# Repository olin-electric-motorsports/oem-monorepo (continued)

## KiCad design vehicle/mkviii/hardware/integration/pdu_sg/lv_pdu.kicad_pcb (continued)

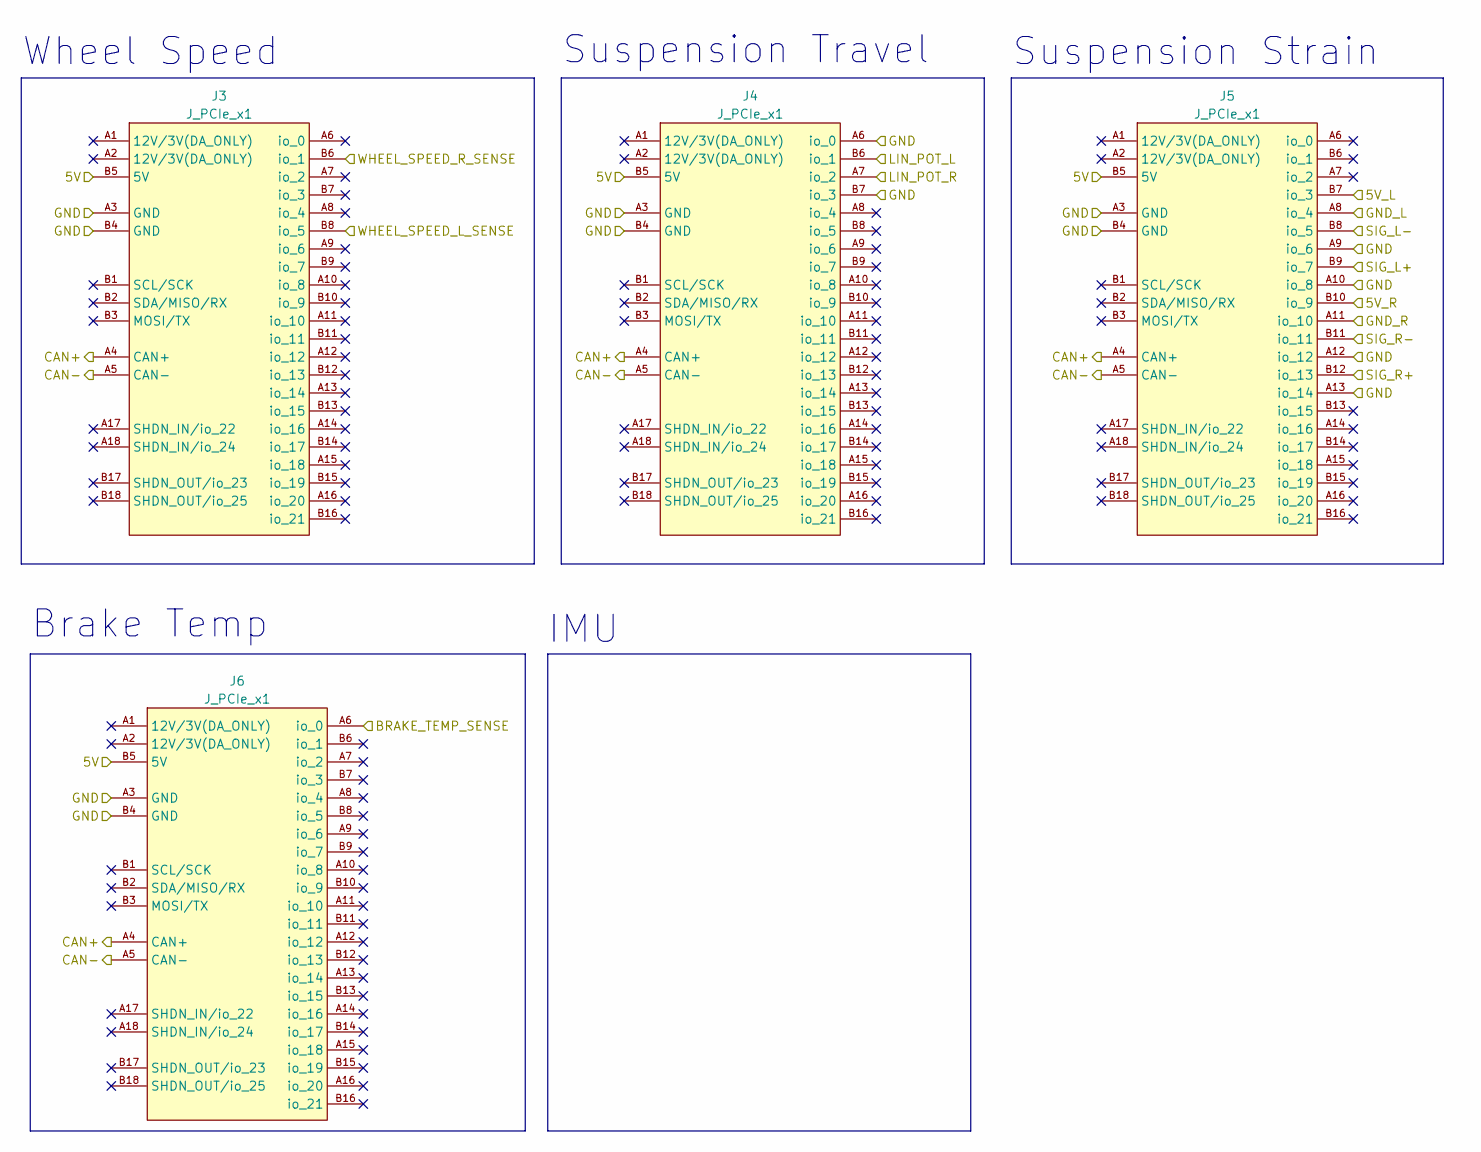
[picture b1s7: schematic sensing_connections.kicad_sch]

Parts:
J3, J4, J5, J6: J_PCIe_x1; MPN 2-1761465-1

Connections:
/BRAKE_TEMP_SIG: J6.A6 (io_0); also elsewhere on the board
/CAN_2+: J3.A4 (CAN+), J4.A4 (CAN+), J5.A4 (CAN+), J6.A4 (CAN+); also elsewhere on the board
/CAN_2-: J3.A5 (CAN-), J4.A5 (CAN-), J5.A5 (CAN-), J6.A5 (CAN-); also elsewhere on the board
/EXCITATION_L+: J5.B7 (io_3); also elsewhere on the board
/EXCITATION_L-: J5.A8 (io_4); also elsewhere on the board
/EXCITATION_R+: J5.B10 (io_9); also elsewhere on the board
/EXCITATION_R-: J5.A11 (io_10); also elsewhere on the board
/SIGNAL_L+: J5.B9 (io_7); also elsewhere on the board
/SIGNAL_L-: J5.B8 (io_5); also elsewhere on the board
/SIGNAL_R+: J5.B12 (io_13); also elsewhere on the board
/SIGNAL_R-: J5.B11 (io_11); also elsewhere on the board
/SUS_TRAVEL_L_SIG: J4.B6 (io_1); also elsewhere on the board
/SUS_TRAVEL_R_SIG: J4.A7 (io_2); also elsewhere on the board
/WHEEL_SPEED_L_SIG: J3.B8 (io_5); also elsewhere on the board
/WHEEL_SPEED_R_SIG: J3.B6 (io_1); also elsewhere on the board
GND: J3.A3 (GND), J3.B4 (GND), J4.A3 (GND), J4.A6 (io_0), J4.B4 (GND), J4.B7 (io_3), J5.A3 (GND), J5.A9 (io_6), J5.A10 (io_8), J5.A12 (io_12), J5.A13 (io_14), J5.B4 (GND), J6.A3 (GND), J6.B4 (GND); also elsewhere on the board

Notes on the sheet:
Brake Temp
Suspension Travel
IMU
Suspension Strain
Wheel Speed

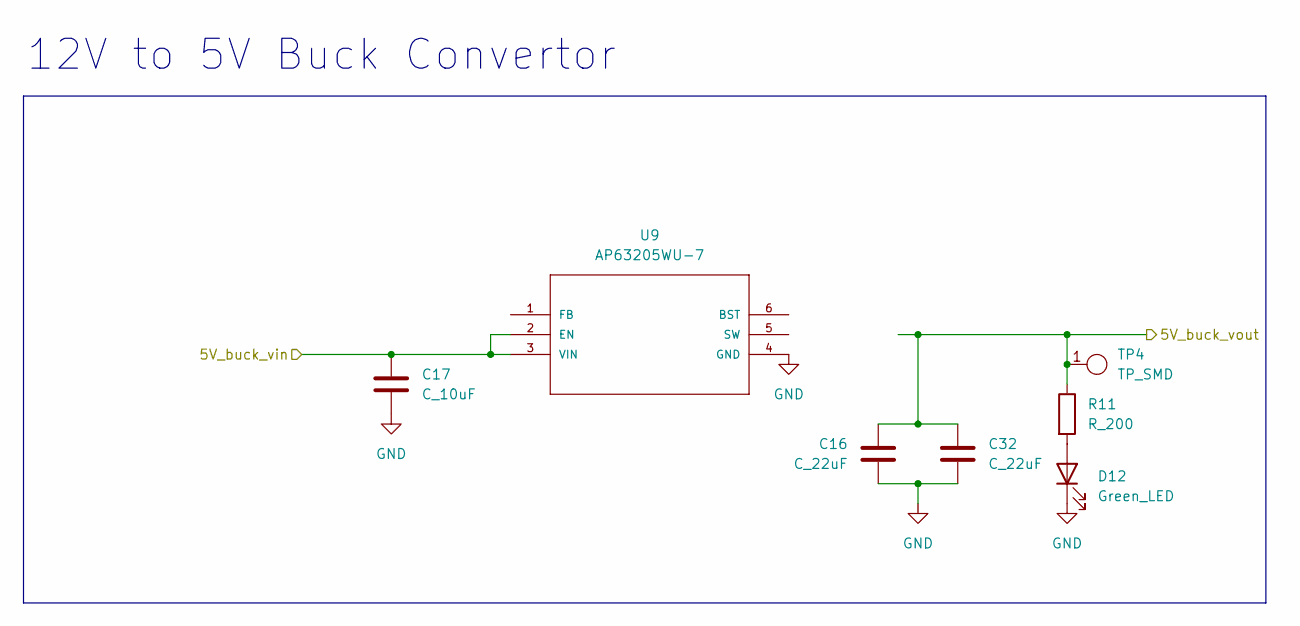
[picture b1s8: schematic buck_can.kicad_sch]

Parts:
C16, C32: C_22uF; C_1206_3216Metric; MPN CL31A226KAHNNNE
C17: C_10uF; C_0603_1608Metric; MPN GRM188D71A106KA73D
D12: Green_LED; D_0805_2012Metric; MPN LTST-C171KRKT
R11: R_200; R_0603_1608Metric; MPN WR06X2000FTL
TP4: TP_SMD; TP_Hook_SMD; MPN 5019
U9: AP63205WU-7; SOIC_05WU-7_DIO-M; MPN AP63205WU-7

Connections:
GND: C16.2, C17.2, C32.2, D12.1 (K), U9.1 (GND), U9.4 (GND); also elsewhere on the board
unnamed: D12.2 (A), R11.2

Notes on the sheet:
12V to 5V Buck Convertor

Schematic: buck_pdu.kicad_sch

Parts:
C18: C_10uF; C_0603_1608Metric; MPN GRM188D71A106KA73D
C19, C20: C_22uF; C_0603_1608Metric; MPN CL31A226KAHNNNE
C21: C_0.1uF; C_0603_1608Metric; MPN C0603C104Z4VACTU
D14: Green_LED; D_0805_2012Metric; MPN LTST-C170KGKT
L1: L_3.9uH; IND_BOURNS_SRR5018 (L_3.9uH_2A_55m_SMD); MPN SRR5018-3R9Y
R13: R_60.4; R_0603_1608Metric; MPN RMCF0603FT60R4
TP5: TP_SMD; TP_Hook_SMD; MPN 5019
U10: AP63203WU-7; SOT-23-6; MPN AP63203WU-7

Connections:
/low voltage distribution/3V3 buck/3V3_buck_vin: C18.1, U10.2 (EN), U10.3 (VIN)
/low voltage distribution/3V3 buck/3V3_buck_vout: C19.1, C20.1, L1.2, R13.1, TP5.1, U10.1 (FB)
GND: C18.2, C19.2, C20.2, D14.1 (K), U10.4 (GND); also elsewhere on the board
unnamed: D14.2 (A), R13.2
unnamed: C21.1, U10.6 (BST)
unnamed: C21.2, L1.1, U10.5 (SW)

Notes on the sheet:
12V to 3V3 Buck Converter

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
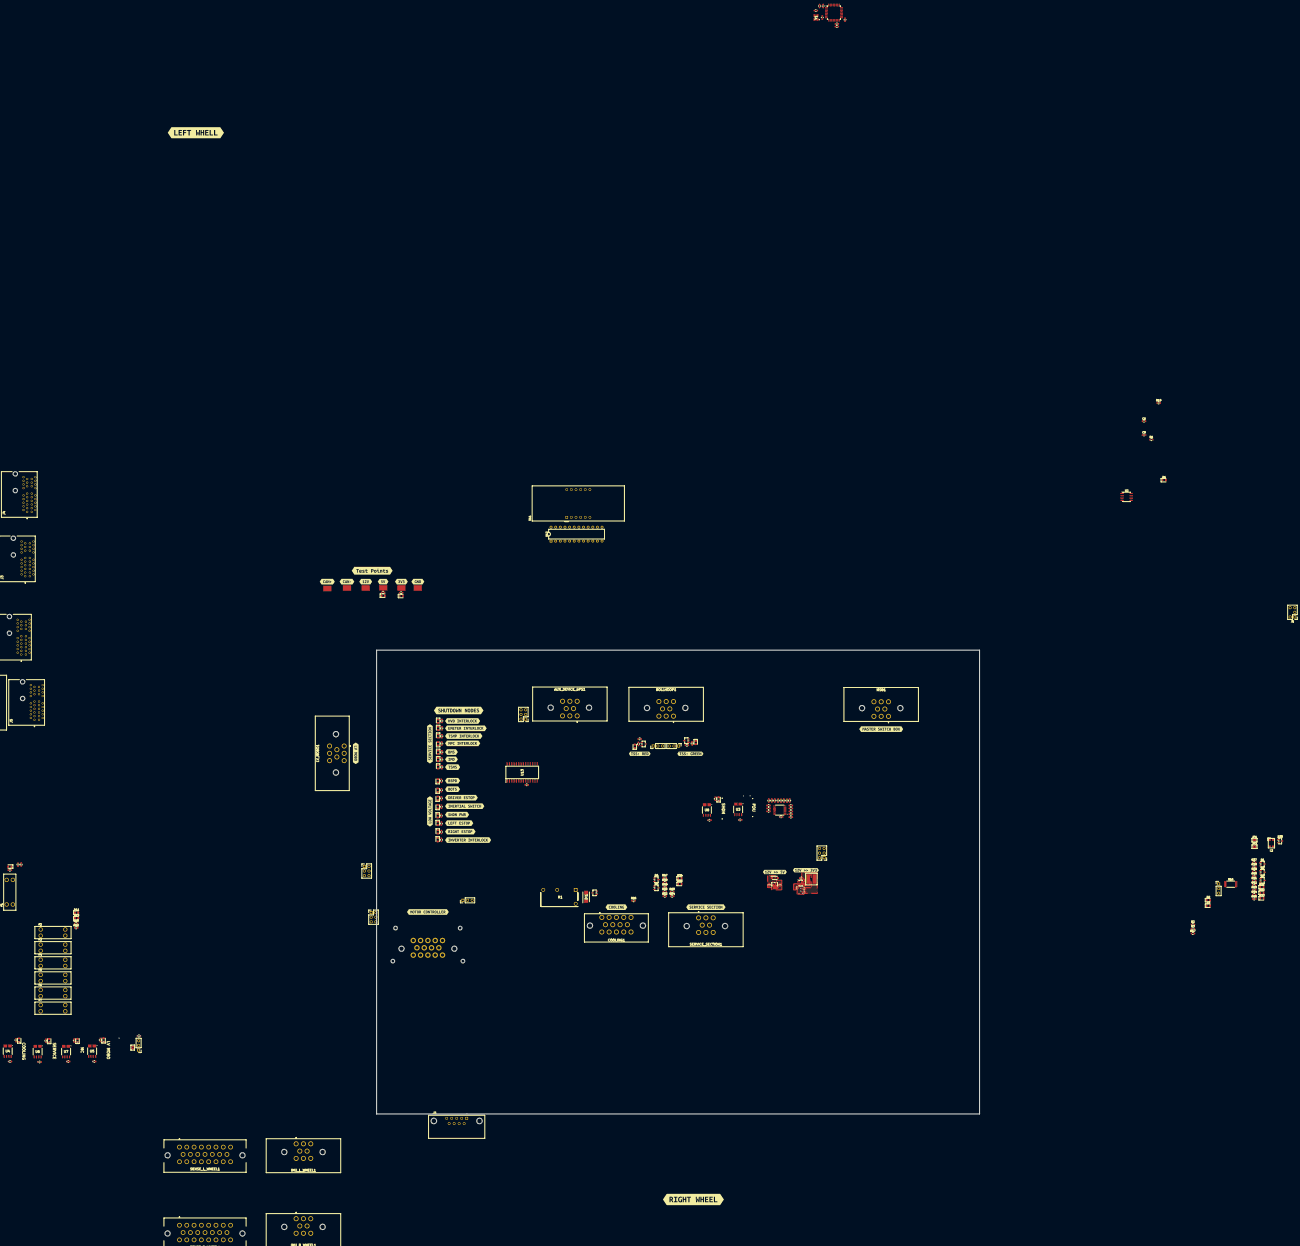
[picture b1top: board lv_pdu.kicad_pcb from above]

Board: 4 copper layers, 330.2 x 254.0 mm, 240 parts (1 on the bottom side), 169 nets.

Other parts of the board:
D10: D_100V_1A; SODFL3718X102N (D_Schottky_100V_1A_SMD - SS110LW)
kibuzzard-6AF3A9EF: G***; kibuzzard-6AF3A9EF
kibuzzard-6AF3AA3E: G***; kibuzzard-6AF3AA3E
kibuzzard-6AF3AA7C: G***; kibuzzard-6AF3AA7C
kibuzzard-6AF3AA54: G***; kibuzzard-6AF3AA54
kibuzzard-6AF3AA92: G***; kibuzzard-6AF3AA92
kibuzzard-6AF3AAA2: G***; kibuzzard-6AF3AAA2
kibuzzard-6AF3AB1F: G***; kibuzzard-6AF3AB1F
kibuzzard-6AF3AB02: G***; kibuzzard-6AF3AB02
kibuzzard-6AF3AB16: G***; kibuzzard-6AF3AB16
kibuzzard-6AF3AB30: G***; kibuzzard-6AF3AB30
kibuzzard-6AF3AC5A: G***; kibuzzard-6AF3AC5A
kibuzzard-6AF3AC21: G***; kibuzzard-6AF3AC21
kibuzzard-6AF3AC46: G***; kibuzzard-6AF3AC46
kibuzzard-6AF3AC51: G***; kibuzzard-6AF3AC51
kibuzzard-6AF3AC73: G***; kibuzzard-6AF3AC73
kibuzzard-6AF3AC82: G***; kibuzzard-6AF3AC82
kibuzzard-6AF3ACA7: G***; kibuzzard-6AF3ACA7
kibuzzard-6AF3ACE3: G***; kibuzzard-6AF3ACE3
kibuzzard-6AF3AD90: G***; kibuzzard-6AF3AD90
kibuzzard-6AF3ADBE: G***; kibuzzard-6AF3ADBE
kibuzzard-6AF3ADF4: G***; kibuzzard-6AF3ADF4
kibuzzard-6AF3AE7A: G***; kibuzzard-6AF3AE7A
kibuzzard-6AF3AEED: G***; kibuzzard-6AF3AEED
kibuzzard-6AF3AF2F: G***; kibuzzard-6AF3AF2F
kibuzzard-6AF3BEE3: G***; kibuzzard-6AF3BEE3
kibuzzard-6AF3BF1E: G***; kibuzzard-6AF3BF1E
kibuzzard-6AF3BF40: G***; kibuzzard-6AF3BF40
kibuzzard-6AF66EEA: G***; kibuzzard-6AF66EEA
kibuzzard-6AF66EF9: G***; kibuzzard-6AF66EF9
kibuzzard-6AF392A3: G***; kibuzzard-6AF392A3
kibuzzard-6AF392F1: G***; kibuzzard-6AF392F1
kibuzzard-6AF3934F: G***; kibuzzard-6AF3934F
kibuzzard-6AF3939E: G***; kibuzzard-6AF3939E
kibuzzard-6AF6706F: G***; kibuzzard-6AF6706F
kibuzzard-6AF6707D: G***; kibuzzard-6AF6707D
kibuzzard-6AF39264: G***; kibuzzard-6AF39264
kibuzzard-6AF39337: G***; kibuzzard-6AF39337
kibuzzard-6AF39365: G***; kibuzzard-6AF39365
kibuzzard-6AF67121: G***; kibuzzard-6AF67121
kibuzzard-6AFCE8DF: G***; kibuzzard-6AFCE8DF

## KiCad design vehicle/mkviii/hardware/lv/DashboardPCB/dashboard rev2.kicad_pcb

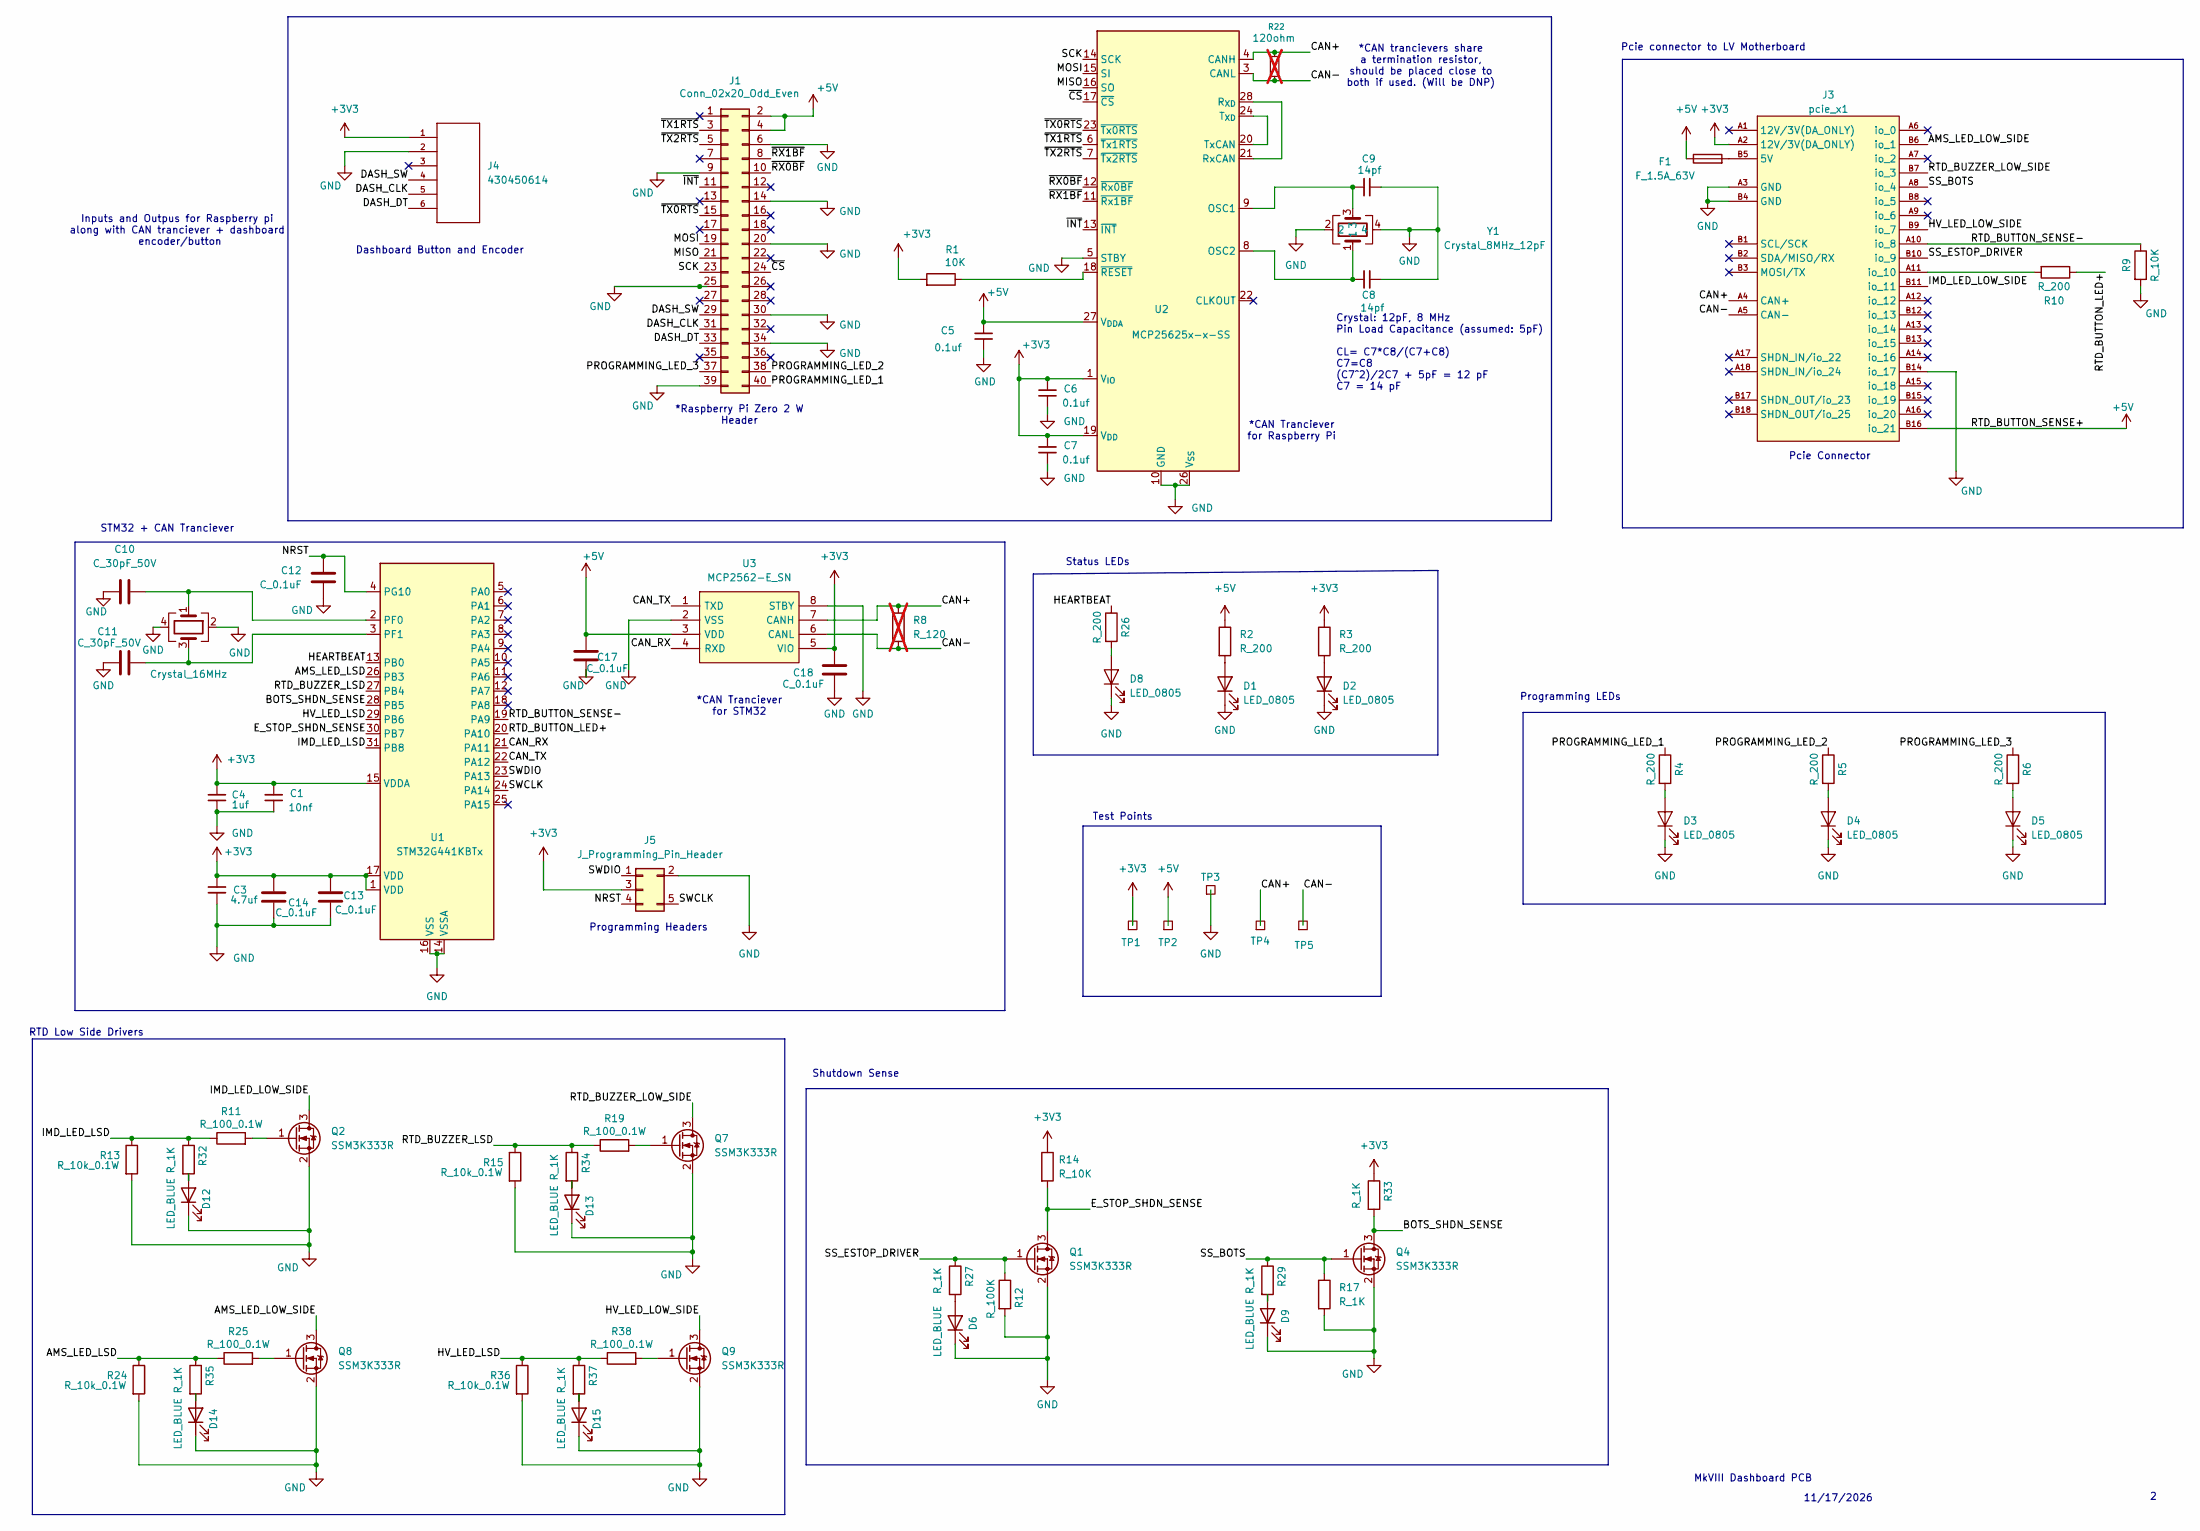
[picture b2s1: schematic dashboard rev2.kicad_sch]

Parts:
C1: 10nf; C_0603_1608Metric
C3: 4.7uf; C_0603_1608Metric
C4: 1uf; C_0603_1608Metric
C5, C6, C7: 0.1uf; C_0603_1608Metric
C8, C9: 14pf; C_0603_1608Metric
C10, C11: C_30pF_50V; C_0603_1608Metric; MPN CML0603C0G300JT50V
C12, C13, C14: C_0.1uF; C_0603_1608Metric; MPN CL10B104KB8NNWC
C17, C18: C_0.1uF; C_0603_1608Metric; MPN C0603C104Z4VACTU
D1, D2, D3, D4, D5, D8: LED_0805; D_0805_2012Metric; MPN 475-1410-1-ND
D6, D9, D12, D13, D14, D15: LED_BLUE; D_0805_2012Metric
F1: F_1.5A_63V; Fuse_1206_3216Metric; MPN 046601.5NR
J1: Conn_02x20_Odd_Even; PinHeader_2x20_P2.54mm_Vertical; MPN SFH11-PBPC-D20-ST-BK
J3: pcie_x1; BUS_PCIexpress_x1
J4: 430450614; MOLEX_0430450600; MANUFACTURER_PART_NUMBER 430450614
J5: J_Programming_Pin_Header; J_Programming_Pin_Header_Keyed
Q1, Q2, Q4, Q7, Q8, Q9: SSM3K333R; SOT-23; MPN SSM3K333RLFCT-ND
R1: 10K; R_0603_1608Metric_Pad0.98x0.95mm_HandSolder; MPN CRS0805-FX-1002ELFCT-ND
R2, R3, R4, R5, R6, R10, R26: R_200; R_0603_1608Metric_Pad0.98x0.95mm_HandSolder; MPN RMCF0805JT200RCT-ND
R8: R_120; R_0603_1608Metric; MPN RC0603FR-13120RL; not fitted
R9, R14: R_10K; R_0603_1608Metric_Pad0.98x0.95mm_HandSolder; MPN CRS0805-FX-1002ELFCT-ND
R11, R19, R25, R38: R_100_0.1W; R_0603_1608Metric; MPN RMCF0603FT100R
R12: R_100K; R_0603_1608Metric_Pad0.98x0.95mm_HandSolder; MPN P100KCCT-ND
R13, R15, R24, R36: R_10k_0.1W; R_0603_1608Metric; MPN RMCF0603FT10K0
R17, R27, R29, R32, R33, R34, R35, R37: R_1K; R_0603_1608Metric_Pad0.98x0.95mm_HandSolder; MPN RNCP0805FTD1K00CT-ND
R22: 120ohm; R_0402_1005Metric_Pad0.72x0.64mm_HandSolder; not fitted
TP1, TP2, TP3, TP4, TP5: TestPoint_Square; Test_Point_SMD
U1: STM32G441KBTx; LQFP-32_7x7mm_P0.8mm
U2: MCP25625x-x-SS; SSOP-28_5.3x10.2mm_P0.65mm
U3: MCP2562-E_SN; SOIC127P600X175-8N; Manufacturer_Part_Number MCP2562-E/SN; Mouser Part Number 579-MCP2562-E/SN
Y1: Crystal_8MHz_12pF; Crystal_TXC7M
Y2: Crystal_16MHz; Crystal_TXC7M; MPN 7M-16.000MAAJ-T

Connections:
+3V3: C1.1, C3.1, C4.1, C6.1, C7.1, C13.1, C14.1, C18.2, J3.A2 (12V/3V(DA_ONLY)), J4.1, J5.3, R1.2, R3.1, R14.1, R33.1, TP1.1 (1_1), U1.1 (VDD), U1.15 (VDDA), U1.17 (VDD), U2.1 (V_{IO}), U2.19 (V_{DD}), U3.5 (VIO)
+5V: C5.2, C17.2, F1.1, J1.2, J1.4, J3.B16 (io_21), R2.1, TP2.1 (1_1), U2.27 (V_{DDA}), U3.3 (VDD)
/AMS_LED_LOW_SIDE: J3.B6 (io_1), Q8.3 (D)
/AMS_LED_LSD: R24.1, R25.1, R35.1, U1.26 (PB3)
/BOTS_SHDN_SENSE: Q4.3 (D), R33.2, U1.28 (PB5)
/CAN+: J3.A4 (CAN+), R8.1, R22.1, TP4.1 (1_1), U2.4 (CANH), U3.7 (CANH)
/CAN-: J3.A5 (CAN-), R8.2, R22.2, TP5.1 (1_1), U2.3 (CANL), U3.6 (CANL)
/CAN_RX: U1.21 (PA11), U3.4 (RXD)
/CAN_TX: U1.22 (PA12), U3.1 (TXD)
/DASH_CLK: J1.31, J4.5
/DASH_DT: J1.33, J4.6
/DASH_SW: J1.29, J4.4
/E_STOP_SHDN_SENSE: Q1.3 (D), R14.2, U1.30 (PB7)
/HEARTBEAT: R26.1, U1.13 (PB0)
/HV_LED_LOW_SIDE: J3.B9 (io_7), Q9.3 (D)
/HV_LED_LSD: R36.1, R37.1, R38.1, U1.29 (PB6)
/IMD_LED_LOW_SIDE: J3.B11 (io_11), Q2.3 (D)
/IMD_LED_LSD: R11.1, R13.1, R32.1, U1.31 (PB8)
/MISO: J1.21, U2.16 (SO)
/MOSI: J1.19, U2.15 (SI)
/NRST: C12.1, J5.4, U1.4 (PG10)
/PROGRAMMING_LED_1: J1.40, R4.1
/PROGRAMMING_LED_2: J1.38, R5.1
/PROGRAMMING_LED_3: J1.37, R6.1
/RTD_BUTTON_LED+: R10.1, U1.20 (PA10)
/RTD_BUTTON_SENSE-: J3.A10 (io_8), R9.1, U1.19 (PA9)
/RTD_BUZZER_LOW_SIDE: J3.B7 (io_3), Q7.3 (D)
/RTD_BUZZER_LSD: R15.1, R19.1, R34.1, U1.27 (PB4)
/SCK: J1.23, U2.14 (SCK)
/SS_BOTS: J3.A8 (io_4), Q4.1 (G), R17.1, R29.1
/SS_ESTOP_DRIVER: J3.B10 (io_9), Q1.1 (G), R12.1, R27.1
/SWCLK: J5.5, U1.24 (PA14)
/SWDIO: J5.1, U1.23 (PA13)
/~CS: J1.24, U2.17 (~CS)
/~INT: J1.11, U2.13 (~INT)
/~RX0BF: J1.10, U2.12 (~Rx0BF)
/~RX1BF: J1.8, U2.11 (~Rx1BF)
/~TX0RTS: J1.15, U2.23 (~Tx0RTS)
/~TX1RTS: J1.3, U2.6 (~Tx1RTS)
/~TX2RTS: J1.5, U2.7 (~Tx2RTS)
GND: C1.2, C3.2, C4.2, C5.1, C6.2, C7.2, C8.1, C9.1, C10.1, C11.1, C12.2, C13.2, C14.2, C17.1, C18.1, D1.1 (K), D2.1 (K), D3.1 (K), D4.1 (K), D5.1 (K), D6.1 (K), D8.1 (K), D9.1 (K), D12.1 (K), D13.1 (K), D14.1 (K), D15.1 (K), J1.6, J1.9, J1.14, J1.20, J1.25, J1.30, J1.34, J1.39, J3.A3 (GND), J3.B4 (GND), J3.B14 (io_17), J4.2, J5.2, Q1.2 (S), Q2.2 (S), Q4.2 (S), Q7.2 (S), Q8.2 (S), Q9.2 (S), R9.2, R12.2, R13.2, R15.2, R17.2, R24.2, R36.2, TP3.1 (1_1), U1.14 (VSSA), U1.16 (VSS), U1.32 (VSS), U2.5 (STBY), U2.10 (GND), U2.26 (V_{SS}), U3.2 (VSS), U3.8 (STBY), Y1.2, Y1.4, Y2.2, Y2.4
unnamed: D1.2 (A), R2.2
unnamed: D2.2 (A), R3.2
unnamed: D3.2 (A), R4.2
unnamed: D4.2 (A), R5.2
unnamed: D5.2 (A), R6.2
unnamed: D6.2 (A), R27.2
unnamed: D8.2 (A), R26.2
unnamed: D9.2 (A), R29.2
unnamed: D12.2 (A), R32.2
unnamed: D13.2 (A), R34.2
unnamed: D14.2 (A), R35.2
unnamed: D15.2 (A), R37.2
unnamed: F1.2, J3.B5 (5V)
unnamed: J3.A11 (io_10), R10.2
unnamed: Q2.1 (G), R11.2
unnamed: Q7.1 (G), R19.2
unnamed: Q8.1 (G), R25.2
unnamed: Q9.1 (G), R38.2
unnamed: C10.2, U1.2 (PF0), Y2.1
unnamed: C11.2, U1.3 (PF1), Y2.3
unnamed: C9.2, U2.9 (OSC1), Y1.3
unnamed: C8.2, U2.8 (OSC2), Y1.1
unnamed: U2.21 (RxCAN), U2.28 (R_{XD})
unnamed: U2.20 (TxCAN), U2.24 (T_{XD})
unnamed: R1.1, U2.18 (~RESET)

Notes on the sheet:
MkVIII Dashboard PCB
*CAN Tranciever for STM32
*Raspberry Pi Zero 2 W Header
Shutdown Sense
Dashboard Button and Encoder
*CAN Tranciever for Raspberry Pi
Pcie connector to LV Motherboard
*CAN trancievers share a termination resistor, should be placed close to both if used. (Will be DNP)
Programming LEDs
RTD Low Side Drivers
Pcie Connector
Inputs and Outpus for Raspberry pi along with CAN tranciever + dashboard encoder/button
11/17/2026
Test Points
Status LEDs
Crystal: 12pF, 8 MHz Pin Load Capacitance (assumed: 5pF) CL= C7*C8/(C7+C8) C7=C8 (C7^2)/2C7 + 5pF = 12 pF C7 = 14 pF
Programming Headers
STM32 + CAN Tranciever

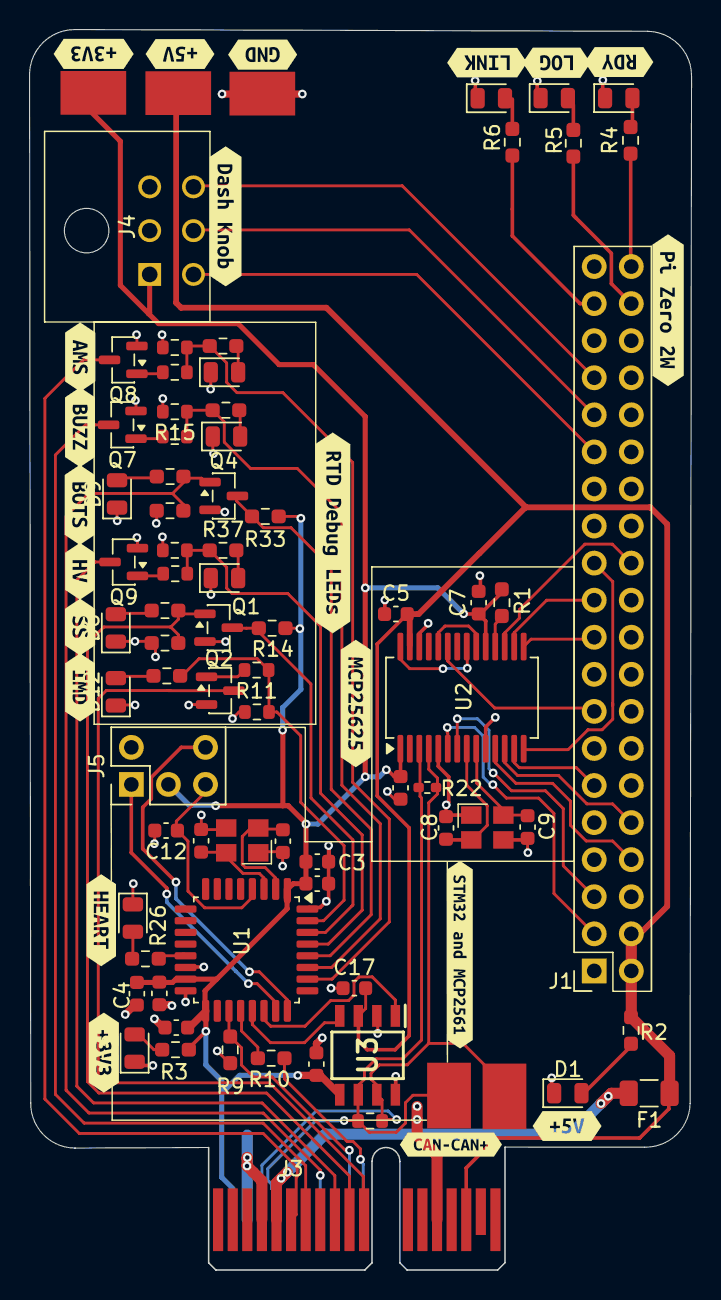
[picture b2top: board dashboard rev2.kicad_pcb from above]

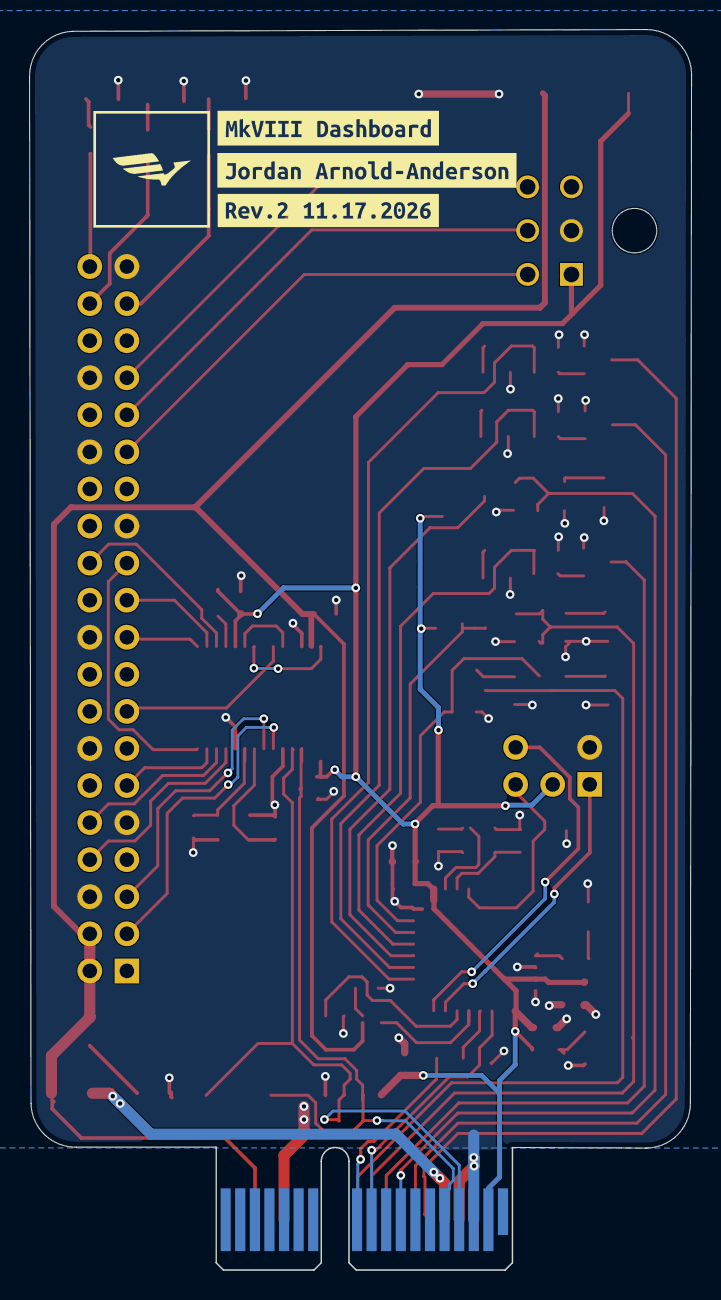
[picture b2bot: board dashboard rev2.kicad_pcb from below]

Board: 2 copper layers, 45.4 x 85.0 mm, 101 parts (4 on the bottom side), 66 nets.

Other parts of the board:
kibuzzard-6AF36B19: G***; kibuzzard-6AF36B19
kibuzzard-6AF76DEC: G***; kibuzzard-6AF76DEC
kibuzzard-6AF76E90: G***; kibuzzard-6AF76E90
kibuzzard-6AF76EA2: G***; kibuzzard-6AF76EA2
kibuzzard-6AF76EB9: G***; kibuzzard-6AF76EB9
kibuzzard-6AF76ED1: G***; kibuzzard-6AF76ED1
kibuzzard-6AF76EDC: G***; kibuzzard-6AF76EDC
kibuzzard-6AF76F0D: G***; kibuzzard-6AF76F0D
kibuzzard-6AF76F2E: G***; kibuzzard-6AF76F2E
kibuzzard-6AF76F8E: G***; kibuzzard-6AF76F8E
kibuzzard-6AF76F23: G***; kibuzzard-6AF76F23
kibuzzard-6AF76F53: G***; kibuzzard-6AF76F53
kibuzzard-6AF76F70: G***; kibuzzard-6AF76F70
kibuzzard-6AF76FEB: G***; kibuzzard-6AF76FEB
kibuzzard-6AF759B2: G***; kibuzzard-6AF759B2
kibuzzard-6AF771E8: G***; kibuzzard-6AF771E8
kibuzzard-6AF771FB: G***; kibuzzard-6AF771FB
kibuzzard-6AF7599B: G***; kibuzzard-6AF7599B
kibuzzard-6AF75395: G***; kibuzzard-6AF75395
kibuzzard-6AF75990: G***; kibuzzard-6AF75990
kibuzzard-6AF77199: G***; kibuzzard-6AF77199
kibuzzard-6AF77208: G***; kibuzzard-6AF77208
kibuzzard-6AFB7252: G***; kibuzzard-6AFB7252
kibuzzard-6AFF5868: G***; kibuzzard-6AFF5868

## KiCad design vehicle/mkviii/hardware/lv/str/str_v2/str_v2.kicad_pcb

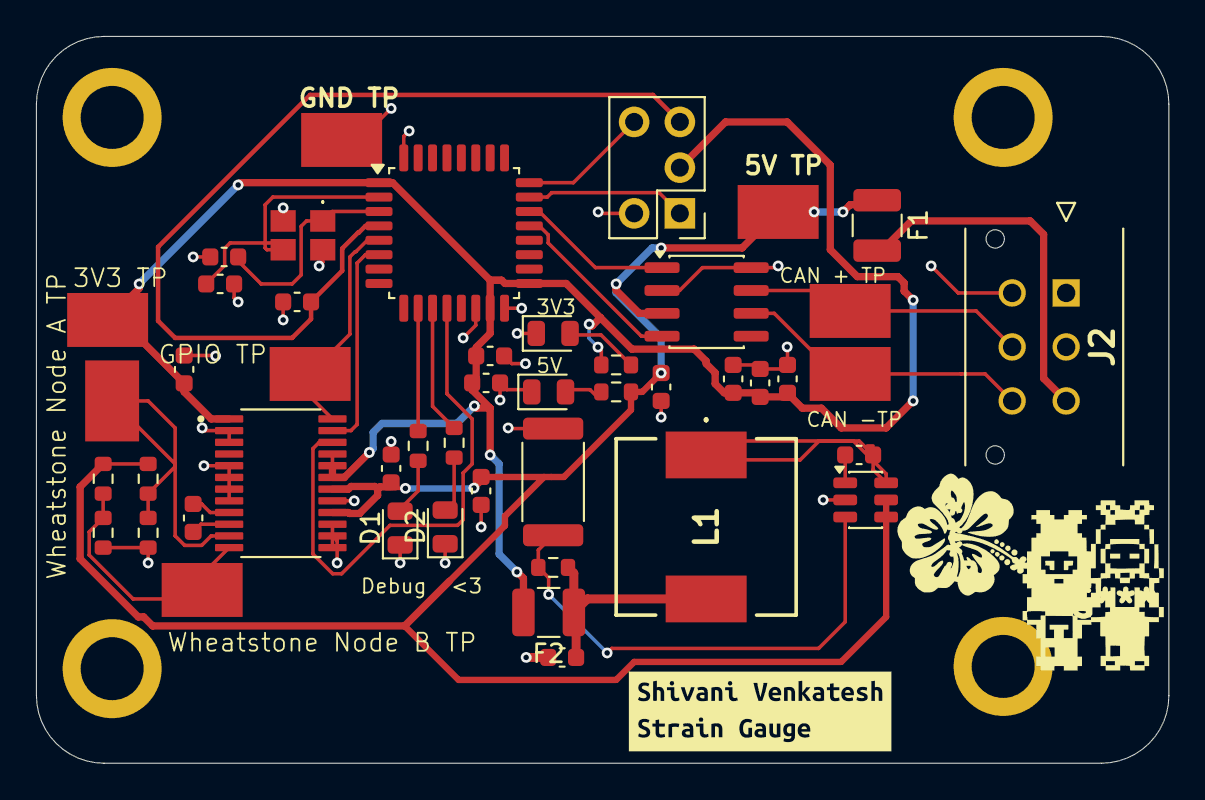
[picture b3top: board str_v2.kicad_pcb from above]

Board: 2 copper layers, 62.9 x 40.4 mm, 53 parts (1 on the bottom side), 30 nets.

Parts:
C1: C_2.2uF; C_0603_1608Metric
C2, C4, C5, C8, C10, C12, C14, C15: C_0.1uF; C_0603_1608Metric
C3, C9: C_10uF; C_0603_1608Metric
C6: C_1uF; C_0603_1608Metric
C7: C_4.7uF; C_0603_1608Metric
C11, C13: C_30pF; C_0603_1608Metric
D1: D_Amber_LED; D_0805_2012Metric
D2, D3, D4: WHITE; D_0805_2012Metric
F1, F2: F_500mA_16V; Fuse_1210_3225Metric
H1, H2, H3, H4: H_MountingHole
J1: J_Programming_Pin_Header; J_Programming_Pin_Header_Keyed
J2: 430450614; J_Molex_Header_02x03_VT - 43045-06YY_121314
L1: L_15uH; NR10050T150M (L_15uH_3.2A_45.5m_SMD - NR10050T150M)
R1: R_49.9k; R_0603_1608Metric
R2: R_20k; R_2512_6332Metric
R4, R5, R6: R_330; R_0603_1608Metric
R7: R_Variable; R_0603_1608Metric
R8, R9, R10, R11: R_1k; R_0603_1608Metric
TP1: TP_SMD; TP_Hook_SMD
TP2, TP3, TP4, TP5, TP6, TP7, TP8: TestPoint; TP_Hook_SMD
U1: LMR50410; SOT-23-6
U2: MCP2561-E_SN; SOIC-8_3.9x4.9mm_P1.27mm
U3: STM32G441KBT6; LQFP-32_7x7mm_P0.8mm
U4: ADC_ADS1232IPW; SOP65P640X120-24N
Y1: X_16MHz_18pF; FA238160000MBC0 (X_16MHz_18pF_SMD - FA-238_16.0000MB-C0)
kibuzzard-6AFFB9C8: G***; kibuzzard-6AFFB9C8
kibuzzard-6AFFBA63: G***; kibuzzard-6AFFBA63

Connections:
+3V3: C2.1, C3.1, C4.1, C6.1, C7.1, C15.2, F2.2, J1.3, R10.2, TP7.1 (1_1), U3.1 (VDD), U3.15 (VDDA), U3.17 (VDD), U4.1 (DVDD), U4.19 (GAIN0), U4.20 (GAIN1), U4.21 (SPEED)
+5V: C1.1, C8.1, C12.2, F1.1, R4.1, R6.1, R11.2, TP2.1 (1_1), U1.4 (EN), U1.5 (VIN), U2.3 (VDD), U4.16 (REFP), U4.18 (AVDD)
/CAN_+: J2.5, TP3.1 (1_1), U2.7 (CANH)
/CAN_-: J2.6, TP4.1 (1_1), U2.6 (CANL)
/CAN_RX: U2.4 (RXD), U3.21 ((FDCAN1_RX/GPIO_EXTI11)PA11)
/CAN_TX: U2.1 (TXD), U3.22 ((FDCAN1_TX/GPIO_EXTI12)PA12)
/DRDY/DOUT-GPIO: TP8.1 (1_1), U3.5 ((TIM2_ETR/TIM2_CH1/GPIO_EXTI0/ADC2_IN1/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), U4.24 (DRDY_DOUT_N)
/NRST: C10.1, J1.4, U3.4 ((GPIO_EXTI10)PG10-NRST)
/PDWN-GPIO: U3.12 ((TIM3_CH2/TIM17_CH1/GPIO_EXTI7/ADC2_IN4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), U4.22 (PDWN_N)
/SCLK-GPIO: U3.6 ((TIM15_CH1N/TIM2_CH2/GPIO_EXTI1/ADC2_IN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), U4.23 (SCLK)
/SWCLK: J1.5, U3.24 ((SYS_JTCK-SWCLK/GPIO_EXTI14)PA14)
/SWDIO: J1.1, U3.23 ((SYS_JTMS-SWDIO/GPIO_EXTI13)PA13)
/_Debug LED: R8.2, U3.10 ((TIM2_ETR/TIM2_CH1/GPIO_EXTI5/ADC2_IN13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)
/_Heartbeat LED: R9.2, U3.11 ((TIM3_CH1/TIM16_CH1/GPIO_EXTI6/ADC2_IN3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)
GND: C1.2, C2.2, C3.2, C4.2, C6.2, C7.2, C8.2, C9.2, C10.2, C11.2, C12.1, C13.2, C15.1, D1.1 (K), D2.1 (K), D3.1 (K), D4.1 (K), H1.1 (1_1), H2.1 (1_1), H3.1 (1_1), H4.1 (1_1), J1.2, J2.4, R2.2, R5.2, R7.2, TP1.1, U1.2 (GND), U2.2 (VSS), U2.8 (STBY), U3.14 (VSSA), U3.16 (VSS), U3.32 (VSS), U4.2 (DGND), U4.3 (CLKIN_XTAL1), U4.5 (DGND), U4.6 (DGND), U4.7 (TEMP), U4.8 (A0), U4.13 (AINN2), U4.14 (AINP2), U4.15 (REFN), U4.17 (AGND), Y1.2, Y1.4
unnamed: C9.1, F2.1, L1.2, R1.1
unnamed: C14.1, U4.9 (CAP)
unnamed: C14.2, U4.10 (CAP)
unnamed: D1.2 (A), R8.1
unnamed: D2.2 (A), R9.1
unnamed: D3.2 (A), R10.1
unnamed: D4.2 (A), R11.1
unnamed: F1.2, J2.3
unnamed: C5.1, U1.1 (CB)
unnamed: R1.2, R2.1, U1.3 (FB)
unnamed: C5.2, L1.1, U1.6 (SW)
unnamed: C13.1, U3.2 (PF0-OSC_IN), Y1.3
unnamed: C11.1, U3.3 (PF1-OSC_OUT), Y1.1
unnamed: R4.2, R5.1, TP5.1 (1_1), U4.12 (AINN1)
unnamed: R6.2, R7.1, TP6.1 (1_1), U4.11 (AINP1)
